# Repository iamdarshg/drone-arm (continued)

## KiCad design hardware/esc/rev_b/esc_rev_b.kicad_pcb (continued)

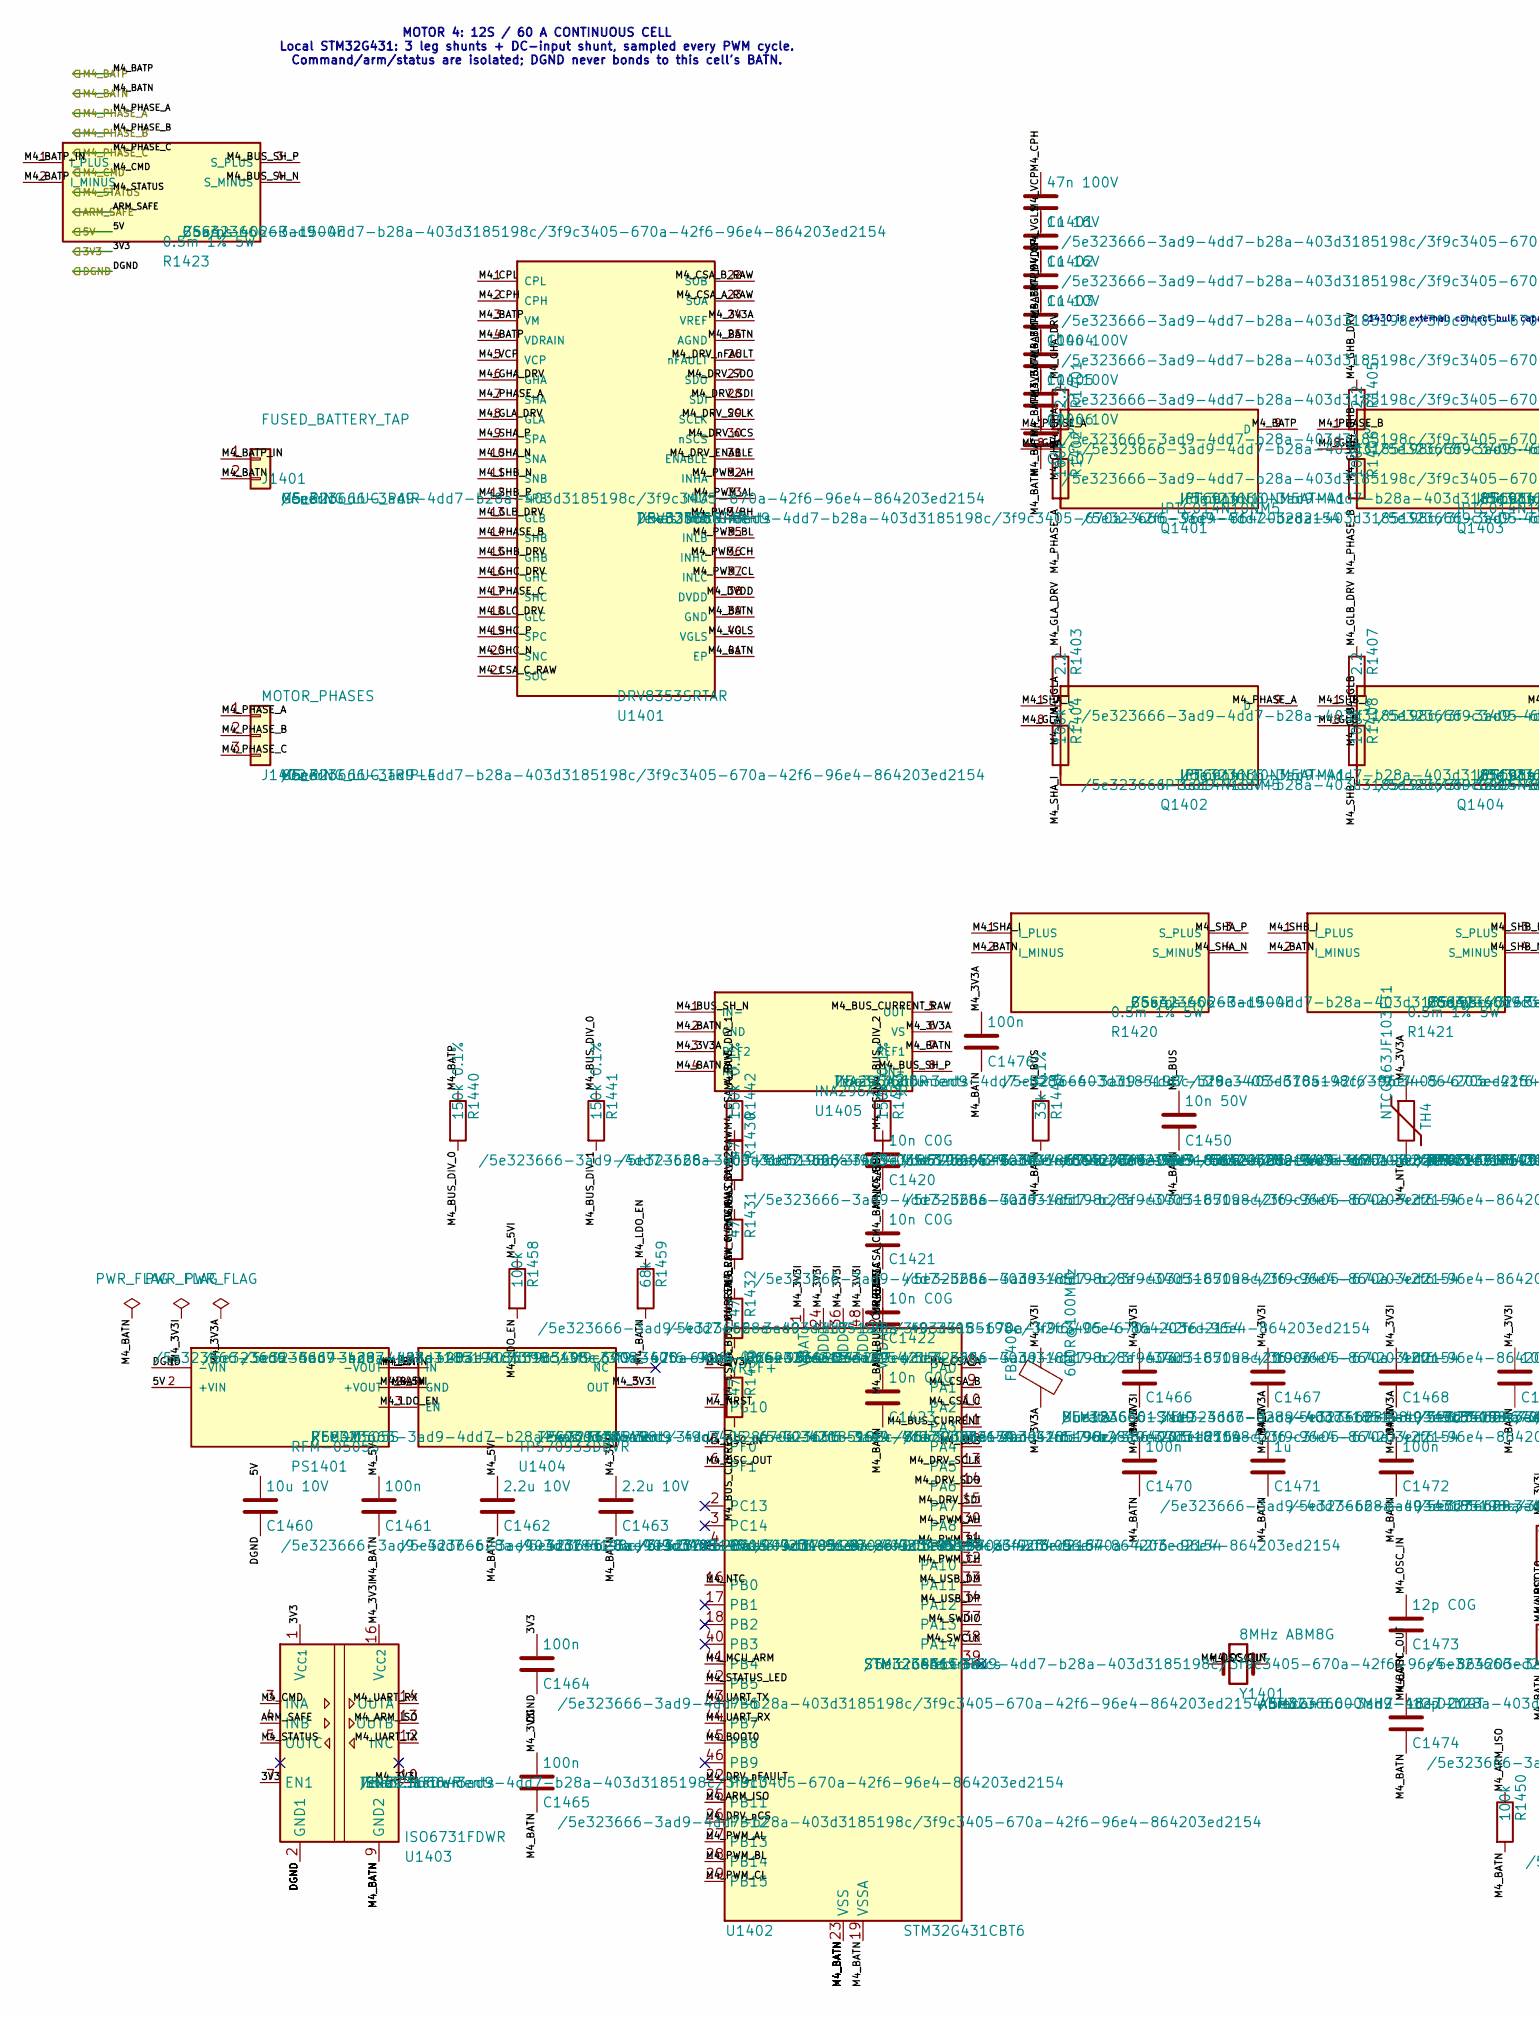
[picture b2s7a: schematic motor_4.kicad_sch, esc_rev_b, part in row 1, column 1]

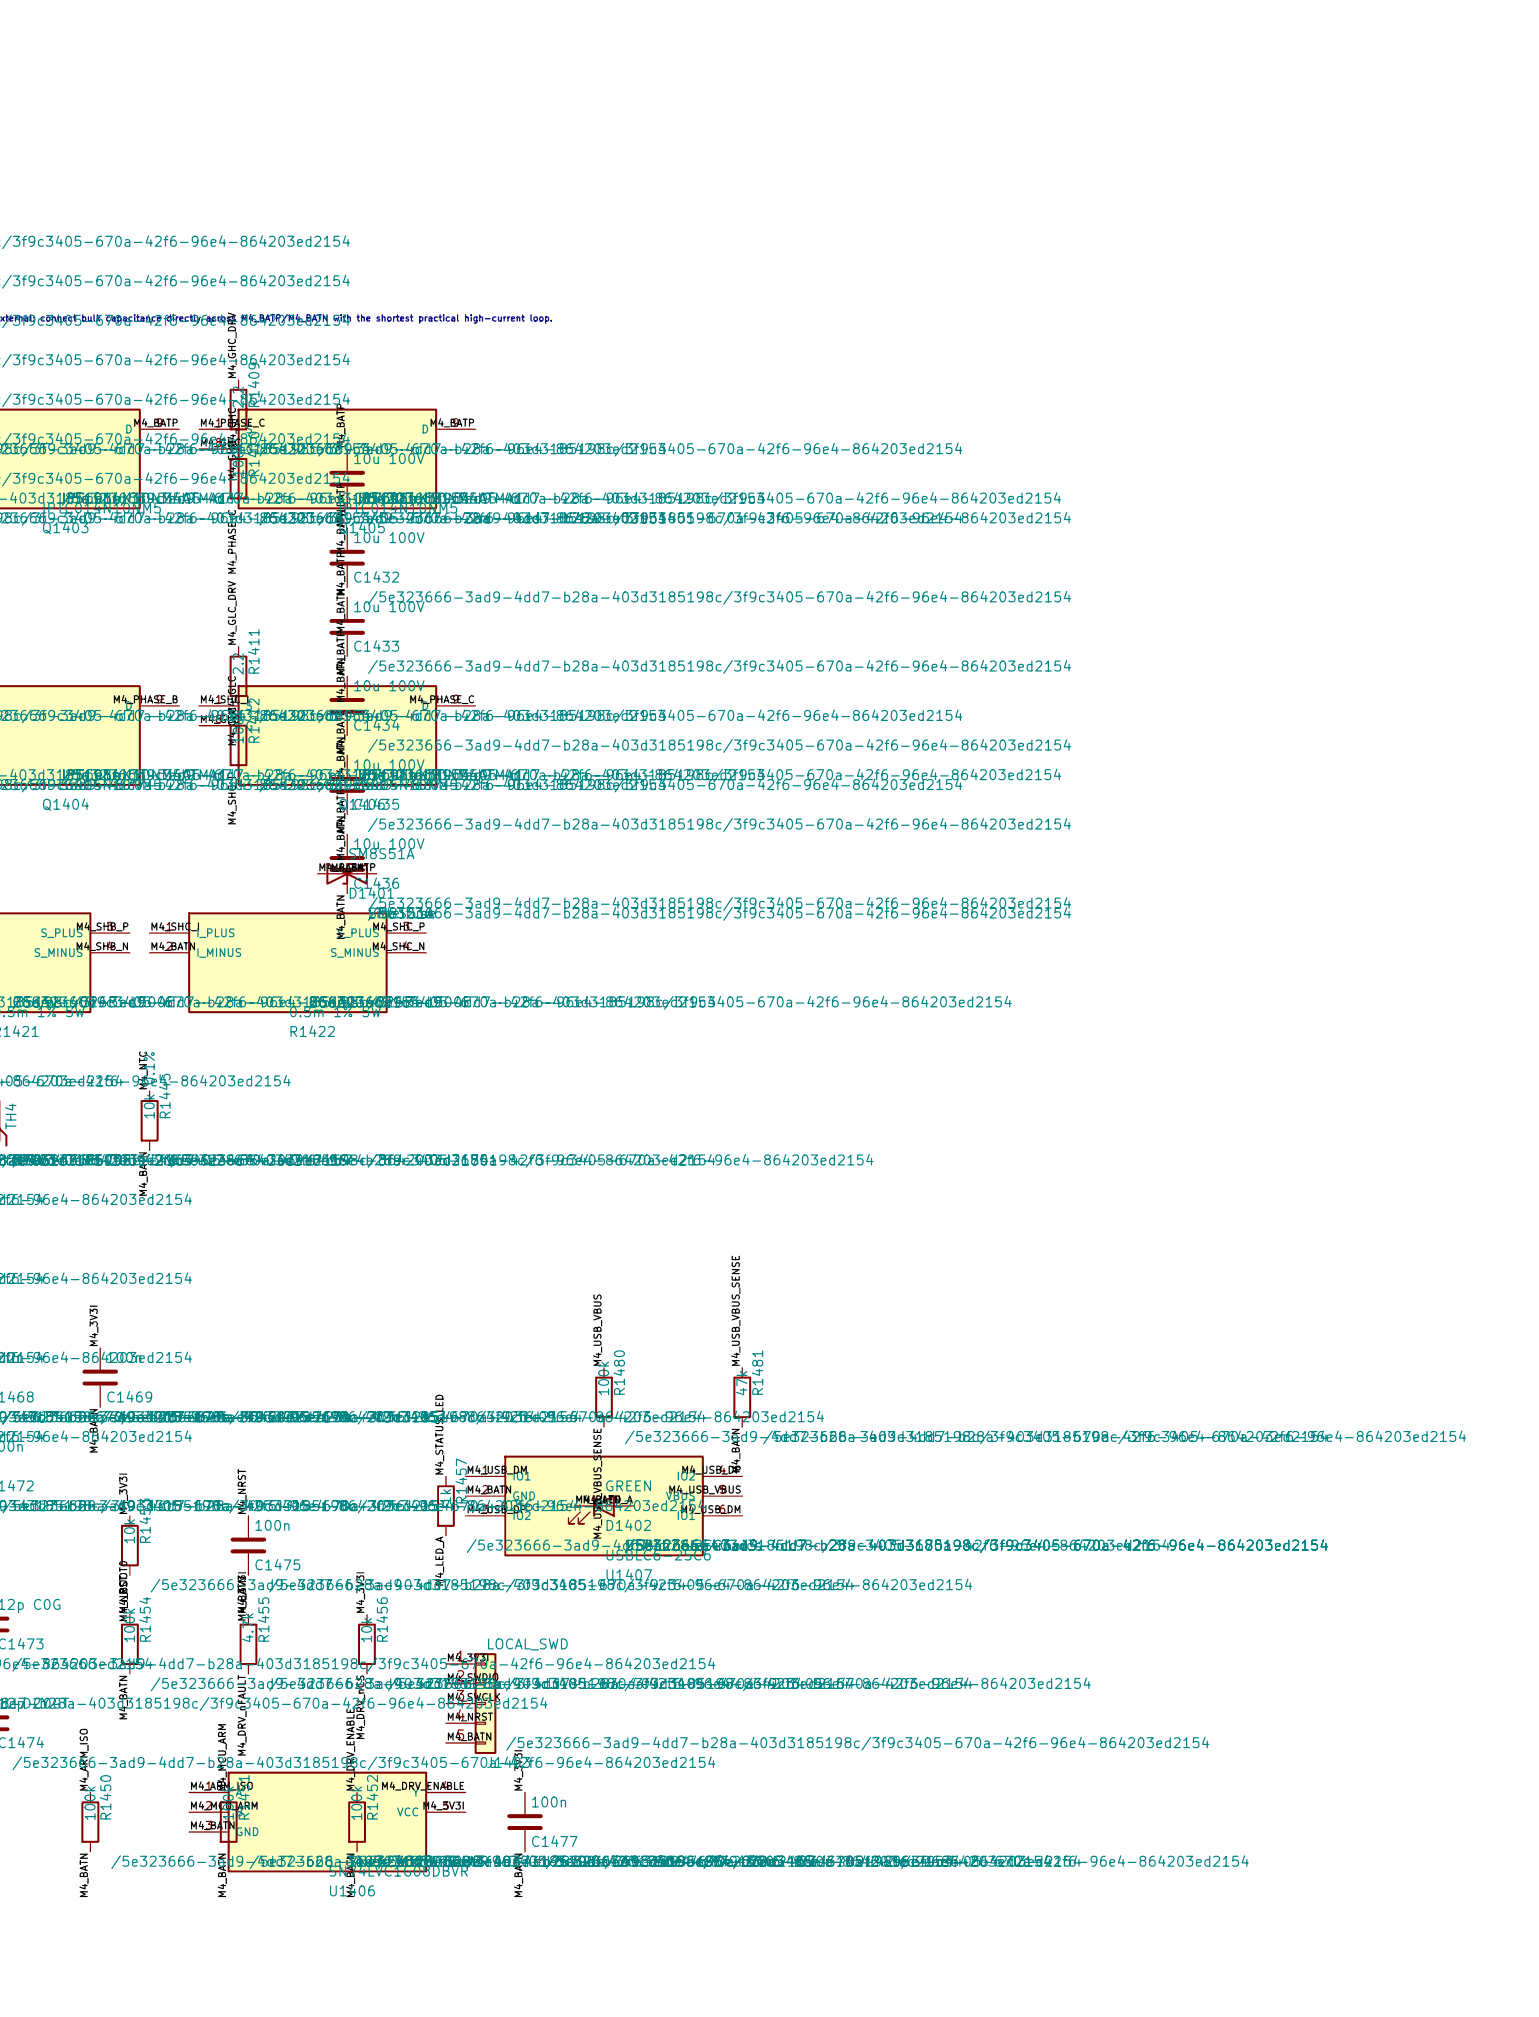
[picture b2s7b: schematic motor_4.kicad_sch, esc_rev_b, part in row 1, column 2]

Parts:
C1401: 47n 100V; C_0603_1608Metric
C1402, C1403: 1u 16V; C_0603_1608Metric
C1404: 1u 10V; C_0603_1608Metric
C1405: 100n 100V; C_0603_1608Metric
C1406, C1431, C1432, C1433, C1434, C1435, C1436: 10u 100V; C_1210_3225Metric
C1407: 100n 10V; C_0603_1608Metric
C1420, C1421, C1422, C1423: 10n C0G; C_0603_1608Metric
C1450: 10n 50V; C_0603_1608Metric
C1460: 10u 10V; C_0805_2012Metric
C1461, C1464, C1465, C1475, C1476, C1477: 100n; C_0603_1608Metric
C1462, C1463: 2.2u 10V; C_0603_1608Metric
C1466: 4.7u; C_0603_1608Metric
C1467, C1468, C1469, C1470, C1472: 100n; C_0402_1005Metric
C1471: 1u; C_0603_1608Metric
C1473, C1474: 12p C0G; C_0402_1005Metric
D1401: SM8S51A; DO-218AB_SM8S; MPN SM8S51A
D1402: GREEN; LED_0603_1608Metric
FB1401: 600R@100MHz; L_0603_1608Metric; MPN BLM18AG601SN1D
J1401: FUSED_BATTERY_TAP; POWER_LUG_M5_2P_P20; MPN M5_RING_LUG_PAIR
J1402: MOTOR_PHASES; POWER_LUG_M5_3P_P20; MPN M5_RING_LUG_TRIPLE
J1403: LOCAL_SWD; PinHeader_1x05_P1.27mm_Vertical
PS1401: RFM-0505S; RFM_SIP4_11.5x6_P2.54; MPN RFM-0505S
Q1401, Q1402, Q1403, Q1404, Q1405, Q1406: IPTC014N10NM5; PG-HDSOP-16_TOLT_IPTC; MPN IPTC014N10NM5ATMA1
R1401, R1403, R1405, R1407, R1409, R1411: 2.2; R_0603_1608Metric
R1402, R1404, R1406, R1408, R1410, R1412, R1450, R1451, R1452, R1454, R1458, R1480: 100k; R_0603_1608Metric
R1420, R1421, R1422, R1423: 0.5m 1% 5W; CSS4J-4026_Kelvin; MPN CSS4J-4026R-L500F
R1430, R1431, R1432, R1433: 47; R_0603_1608Metric
R1440, R1441, R1442, R1443: 150k 0.1%; R_1206_3216Metric
R1444: 33k 0.1%; R_0603_1608Metric
R1445: 10k 0.1%; R_0603_1608Metric
R1453, R1456: 10k; R_0603_1608Metric
R1455: 4.7k; R_0603_1608Metric
R1457: 1k; R_0603_1608Metric
R1459: 68k; R_0603_1608Metric
R1481: 47k; R_0603_1608Metric
TH4: NTCG163JF103FT1; R_0603_1608Metric; MPN NTCG163JF103FT1
U1401: DRV8353SRTAR; WQFN-40-EP_6x6_P0.5; MPN DRV8353SRTAR
U1402: STM32G431CBT6; LQFP-48_7x7mm_P0.5mm; MPN STM32G431CBT6
U1403: ISO6731FDWR; SOIC-16W_7.5x10.3mm_P1.27mm; MPN ISO6731FDWR
U1404: TPS70933DBVR; SOT-23-5; MPN TPS70933DBVR
U1405: INA296A2IDR; SOIC-8_3.9x4.9mm_P1.27mm; MPN INA296A2IDR
U1406: SN74LVC1G08DBVR; SOT-23-5; MPN SN74LVC1G08DBVR
U1407: USBLC6-2SC6; SOT-23-6; MPN USBLC6-2SC6
Y1401: 8MHz ABM8G; Crystal_SMD_3225-4Pin_3.2x2.5mm; MPN ABM8G-8.000MHZ-18-D2Y-T

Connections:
/3V3: C1464.1, U1403.1 (V_{CC1}), U1403.7 (EN1); also elsewhere on the board
/5V: C1460.1, PS1401.2 (+VIN); also elsewhere on the board
/ARM_SAFE: U1403.4 (INB); also elsewhere on the board
/DGND: C1460.2, C1464.2, PS1401.1 (-VIN), U1403.2 (GND1), U1403.8 (GND1); also elsewhere on the board
/M4_BATN: C1403.2, C1404.2, C1405.2, C1406.2, C1407.2, C1420.2, C1421.2, C1422.2, C1423.2, C1431.2, C1432.2, C1433.2, C1434.2, C1435.2, C1436.2, C1450.2, C1461.2, C1462.2, C1463.2, C1465.2, C1466.2, C1467.2, C1468.2, C1469.2, C1470.2, C1471.2, C1472.2, C1473.2, C1474.2, C1475.2, C1476.2, C1477.2, D1401.1 (A1), D1402.1 (K), J1401.2, J1403.5, PS1401.3 (-VOUT), R1420.2 (I_MINUS), R1421.2 (I_MINUS), R1422.2 (I_MINUS), R1444.2, R1445.2, R1450.2, R1451.2, R1452.2, R1454.2, R1459.2, R1481.2, U1401.25 (AGND), U1401.39 (GND), U1401.41 (EP), U1402.19 (VSSA), U1402.23 (VSS), U1402.35 (VSS), U1402.47 (VSS), U1403.9 (GND2), U1403.15 (GND2), U1404.2 (GND), U1405.2 (GND), U1405.4 (NC), U1405.7 (REF1), U1406.3 (GND), U1407.2 (GND); also elsewhere on the board
/M4_BATP: C1402.2, C1405.1, C1406.1, C1431.1, C1432.1, C1433.1, C1434.1, C1435.1, C1436.1, D1401.2 (A2), Q1401.9 (D), Q1403.9 (D), Q1405.9 (D), R1423.2 (I_MINUS), R1440.1, U1401.3 (VM), U1401.4 (VDRAIN); also elsewhere on the board
/M4_CMD: U1403.3 (INA); also elsewhere on the board
/M4_PHASE_A: J1402.1, Q1401.1 (S), Q1402.9 (D), R1402.2, U1401.7 (SHA)
/M4_PHASE_B: J1402.2, Q1403.1 (S), Q1404.9 (D), R1406.2, U1401.14 (SHB)
/M4_PHASE_C: J1402.3, Q1405.1 (S), Q1406.9 (D), R1410.2, U1401.17 (SHC)
/M4_STATUS: U1403.5 (OUTC); also elsewhere on the board
/Motor 4 power cell/M4_3V3A: C1407.1, C1471.1, C1472.1, C1476.1, FB1401.2, TH4.1, U1401.24 (VREF), U1402.20 (VREF+), U1402.21 (VDDA), U1405.3 (REF2), U1405.6 (VS)
/Motor 4 power cell/M4_3V3I: C1463.1, C1465.1, C1466.1, C1467.1, C1468.1, C1469.1, C1470.1, C1477.1, FB1401.1, J1403.1, R1453.1, R1455.1, R1456.1, U1402.1 (VBAT), U1402.24 (VDD), U1402.36 (VDD), U1402.48 (VDD), U1403.10 (EN2), U1403.16 (V_{CC2}), U1404.5 (OUT), U1406.5 (VCC)
/Motor 4 power cell/M4_5VI: C1461.1, C1462.1, PS1401.4 (+VOUT), R1458.1, U1404.1 (IN)
/Motor 4 power cell/M4_ARM_ISO: R1450.1, U1402.25 (PB11), U1403.13 (OUTB), U1406.1 (A)
/Motor 4 power cell/M4_BATP_IN: J1401.1, R1423.1 (I_PLUS)
/Motor 4 power cell/M4_BOOT0: R1454.1, U1402.45 (PB8)
/Motor 4 power cell/M4_BUS: C1450.1, R1443.2, R1444.1, U1402.12 (PA4)
/Motor 4 power cell/M4_BUS_CURRENT: C1423.1, R1433.2, U1402.11 (PA3)
/Motor 4 power cell/M4_BUS_CURRENT_RAW: R1433.1, U1405.5 (OUT)
/Motor 4 power cell/M4_BUS_DIV_0: R1440.2, R1441.1
/Motor 4 power cell/M4_BUS_DIV_1: R1441.2, R1442.1
/Motor 4 power cell/M4_BUS_DIV_2: R1442.2, R1443.1
/Motor 4 power cell/M4_BUS_SH_N: R1423.4 (S_MINUS), U1405.1 (IN-)
/Motor 4 power cell/M4_BUS_SH_P: R1423.3 (S_PLUS), U1405.8 (IN+)
/Motor 4 power cell/M4_CPH: C1401.1, U1401.2 (CPH)
/Motor 4 power cell/M4_CPL: C1401.2, U1401.1 (CPL)
/Motor 4 power cell/M4_CSA_A: C1420.1, R1430.2, U1402.8 (PA0)
/Motor 4 power cell/M4_CSA_A_RAW: R1430.1, U1401.23 (SOA)
/Motor 4 power cell/M4_CSA_B: C1421.1, R1431.2, U1402.9 (PA1)
/Motor 4 power cell/M4_CSA_B_RAW: R1431.1, U1401.22 (SOB)
/Motor 4 power cell/M4_CSA_C: C1422.1, R1432.2, U1402.10 (PA2)
/Motor 4 power cell/M4_CSA_C_RAW: R1432.1, U1401.21 (SOC)
/Motor 4 power cell/M4_DRV_ENABLE: R1452.1, U1401.31 (ENABLE), U1406.4 (Y)
/Motor 4 power cell/M4_DRV_SCLK: U1401.29 (SCLK), U1402.13 (PA5)
/Motor 4 power cell/M4_DRV_SDI: U1401.28 (SDI), U1402.15 (PA7)
/Motor 4 power cell/M4_DRV_SDO: U1401.27 (SDO), U1402.14 (PA6)
/Motor 4 power cell/M4_DRV_nCS: R1456.2, U1401.30 (nSCS), U1402.26 (PB12)
/Motor 4 power cell/M4_DRV_nFAULT: R1455.2, U1401.26 (nFAULT), U1402.22 (PB10)
/Motor 4 power cell/M4_DVDD: C1404.1, U1401.38 (DVDD)
/Motor 4 power cell/M4_GHA: Q1401.8 (G), R1401.2, R1402.1
/Motor 4 power cell/M4_GHA_DRV: R1401.1, U1401.6 (GHA)
/Motor 4 power cell/M4_GHB: Q1403.8 (G), R1405.2, R1406.1
/Motor 4 power cell/M4_GHB_DRV: R1405.1, U1401.15 (GHB)
/Motor 4 power cell/M4_GHC: Q1405.8 (G), R1409.2, R1410.1
/Motor 4 power cell/M4_GHC_DRV: R1409.1, U1401.16 (GHC)
/Motor 4 power cell/M4_GLA: Q1402.8 (G), R1403.2, R1404.1
/Motor 4 power cell/M4_GLA_DRV: R1403.1, U1401.8 (GLA)
/Motor 4 power cell/M4_GLB: Q1404.8 (G), R1407.2, R1408.1
/Motor 4 power cell/M4_GLB_DRV: R1407.1, U1401.13 (GLB)
/Motor 4 power cell/M4_GLC: Q1406.8 (G), R1411.2, R1412.1
/Motor 4 power cell/M4_GLC_DRV: R1411.1, U1401.18 (GLC)
/Motor 4 power cell/M4_LDO_EN: R1458.2, R1459.1, U1404.3 (EN)
/Motor 4 power cell/M4_LED_A: D1402.2 (A), R1457.2
/Motor 4 power cell/M4_MCU_ARM: R1451.1, U1402.41 (PB4), U1406.2 (B)
/Motor 4 power cell/M4_NRST: C1475.1, J1403.4, R1453.2, U1402.7 (PG10)
/Motor 4 power cell/M4_NTC: R1445.1, TH4.2, U1402.16 (PB0)
/Motor 4 power cell/M4_OSC_IN: C1473.1, U1402.5 (PF0), Y1401.1
/Motor 4 power cell/M4_OSC_OUT: C1474.1, U1402.6 (PF1), Y1401.2
/Motor 4 power cell/M4_PWM_AH: U1401.32 (INHA), U1402.30 (PA8)
/Motor 4 power cell/M4_PWM_AL: U1401.33 (INLA), U1402.27 (PB13)
/Motor 4 power cell/M4_PWM_BH: U1401.34 (INHB), U1402.31 (PA9)
/Motor 4 power cell/M4_PWM_BL: U1401.35 (INLB), U1402.28 (PB14)
/Motor 4 power cell/M4_PWM_CH: U1401.36 (INHC), U1402.32 (PA10)
/Motor 4 power cell/M4_PWM_CL: U1401.37 (INLC), U1402.29 (PB15)
/Motor 4 power cell/M4_SHA_I: Q1402.1 (S), R1404.2, R1420.1 (I_PLUS)
/Motor 4 power cell/M4_SHA_N: R1420.4 (S_MINUS), U1401.10 (SNA)
/Motor 4 power cell/M4_SHA_P: R1420.3 (S_PLUS), U1401.9 (SPA)
/Motor 4 power cell/M4_SHB_I: Q1404.1 (S), R1408.2, R1421.1 (I_PLUS)
/Motor 4 power cell/M4_SHB_N: R1421.4 (S_MINUS), U1401.11 (SNB)
/Motor 4 power cell/M4_SHB_P: R1421.3 (S_PLUS), U1401.12 (SPB)
/Motor 4 power cell/M4_SHC_I: Q1406.1 (S), R1412.2, R1422.1 (I_PLUS)
/Motor 4 power cell/M4_SHC_N: R1422.4 (S_MINUS), U1401.20 (SNC)
/Motor 4 power cell/M4_SHC_P: R1422.3 (S_PLUS), U1401.19 (SPC)
/Motor 4 power cell/M4_STATUS_LED: R1457.1, U1402.42 (PB5)
/Motor 4 power cell/M4_SWCLK: J1403.3, U1402.38 (PA14)
/Motor 4 power cell/M4_SWDIO: J1403.2, U1402.37 (PA13)
/Motor 4 power cell/M4_UART_RX: U1402.44 (PB7), U1403.14 (OUTA)
/Motor 4 power cell/M4_UART_TX: U1402.43 (PB6), U1403.12 (INC)
/Motor 4 power cell/M4_USB_DM: U1402.33 (PA11), U1407.1 (IO1), U1407.6 (IO1)
/Motor 4 power cell/M4_USB_DP: U1402.34 (PA12), U1407.3 (IO2), U1407.4 (IO2)
/Motor 4 power cell/M4_USB_VBUS: R1480.1, U1407.5 (VBUS)
/Motor 4 power cell/M4_USB_VBUS_SENSE: R1480.2, R1481.1
/Motor 4 power cell/M4_VCP: C1402.1, U1401.5 (VCP)
/Motor 4 power cell/M4_VGLS: C1403.1, U1401.40 (VGLS)

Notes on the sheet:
MOTOR 4: 12S / 60 A CONTINUOUS CELL Local STM32G431: 3 leg shunts + DC-input shunt, sampled every PWM cycle. Command/arm/status are isolated; DGND never bonds to this cell's BATN.
C1430 is external: connect bulk capacitance directly across M4_BATP/M4_BATN with the shortest practical high-current loop.
